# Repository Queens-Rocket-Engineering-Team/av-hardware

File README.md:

# Avionics Hardware
> 2026-2027 SRAD Avionics Hardware Repository

This repository contains **schematics**, **PCB layouts**, and related **documentation and datasheets** for QRET SRAD Avionics. 
- All ECAD was designed in or transferred to **KiCad 10**.
- Covers **all** avionics systems, including power, propulsion, recovery, telemetry, and shared libraries.
- The **main** branch contains the latest stable hardware that is not currently under active development.
- If you're contributing, please read over the [`Development Standards`](#development-standards) section.
---

## Folder Structure
Avionics systems are organized into root-level directories (e.g., `power/`, `telemetry/`, etc.). 

Each system contains folders per boards and a respective documentation file `README.MD`

Each board follows the structure below:
- `docs`: Board-specific documentation, datasheets, and other reference materials. 
- `symbols`: Board-specific schematic symbols.
- `footprints`: Board-specific PCB footprints.
- `models`: Board-specific component 3D-models.

**Example Structure**
```
av-hardware/
  power/
    README.md
    power-module/
      power-module.kicad_pro
      power-module.kicad_sch
      power-module.kicad_pcb
      docs/
        README.md
        datasheets/
      symbols/
      footprints/
      models/
```

## Development Standards
- **Always** ensure you've fetched and pulled from Git before contributing.
```
git fetch origin
git pull
```
- Keep `main` stable. Never make changes directly on `main`.
- If contributing, use focused, concise, and descriptive branch names and commit messages. Look at standards below.
- Commit changes on your branch frequently, don't leave changes hanging.

### Datasheet Naming Convention
- For ICs and other active components, download and attach the component's datasheet with the following name convention:
`[type]-[part-number].pdf`

For example:
- `ADC-ADS131M04.pdf`
  
### Branches
Contribute by creating a branch.

**Naming Conventions**
- Creating a new board: `dev/<description>`
- Updating or adding a feature to an existing board: `feature/board/<description>`
- Resolving an issue on an existing board: `fix/board/<description>`
- Updating documentation and reference materials: `docs/<description>`

For example:
- `dev/camera-module`
- `feature/power-module/change-buck`
- `fix/lcm/can-trx`

### Commits
Commit messages should be focused, concise, and descriptive. Each commit should represent a single logical change.
- You should try and commit after making a **single change**, rather than committing for several changes at once.

**Examples**
```text
Setup schematic env for camera module
Tune differential pair lengths
Update comms module with new LoRa module
Review updated comms module
```

### Pull Requests
Pull requests should clearly describe the changes being introduced and their purpose.

Before opening a pull request:

- Ensure the branch is up to date with `main`.
- Ensure all work and changes are peer-reviewed in person during meetings or office hours.
- Confirm that no unrelated changes are included.

**Title Convention**

```text
<type/board-name>: <short-description>
```
For example:
```text
feature/power-module: Change buck converter
fix/lcm: Switch to standard CAN transceiver
dev/camera-module: Initial design
docs/gps-antenna: Add images to documentation
```

## Comments
- You will likely encounter different schematic "formats" as you look through this repository. As of 2026, we are pushing the use of **hierarchical sheets** to improve modularity and readability. Previously, schematics were designed on a single, large sheet.

If you're ever unsure about anything, reach out to one us leads!!

---
QRET, 2026-2027

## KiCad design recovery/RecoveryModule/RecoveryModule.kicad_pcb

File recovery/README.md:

# [System Name]

this is a template and will be filled out soon

[Description of the  system and its purpose]

## Boards

- `[board-name]` - Brief description
- ...

---
QRET, 2026-2027

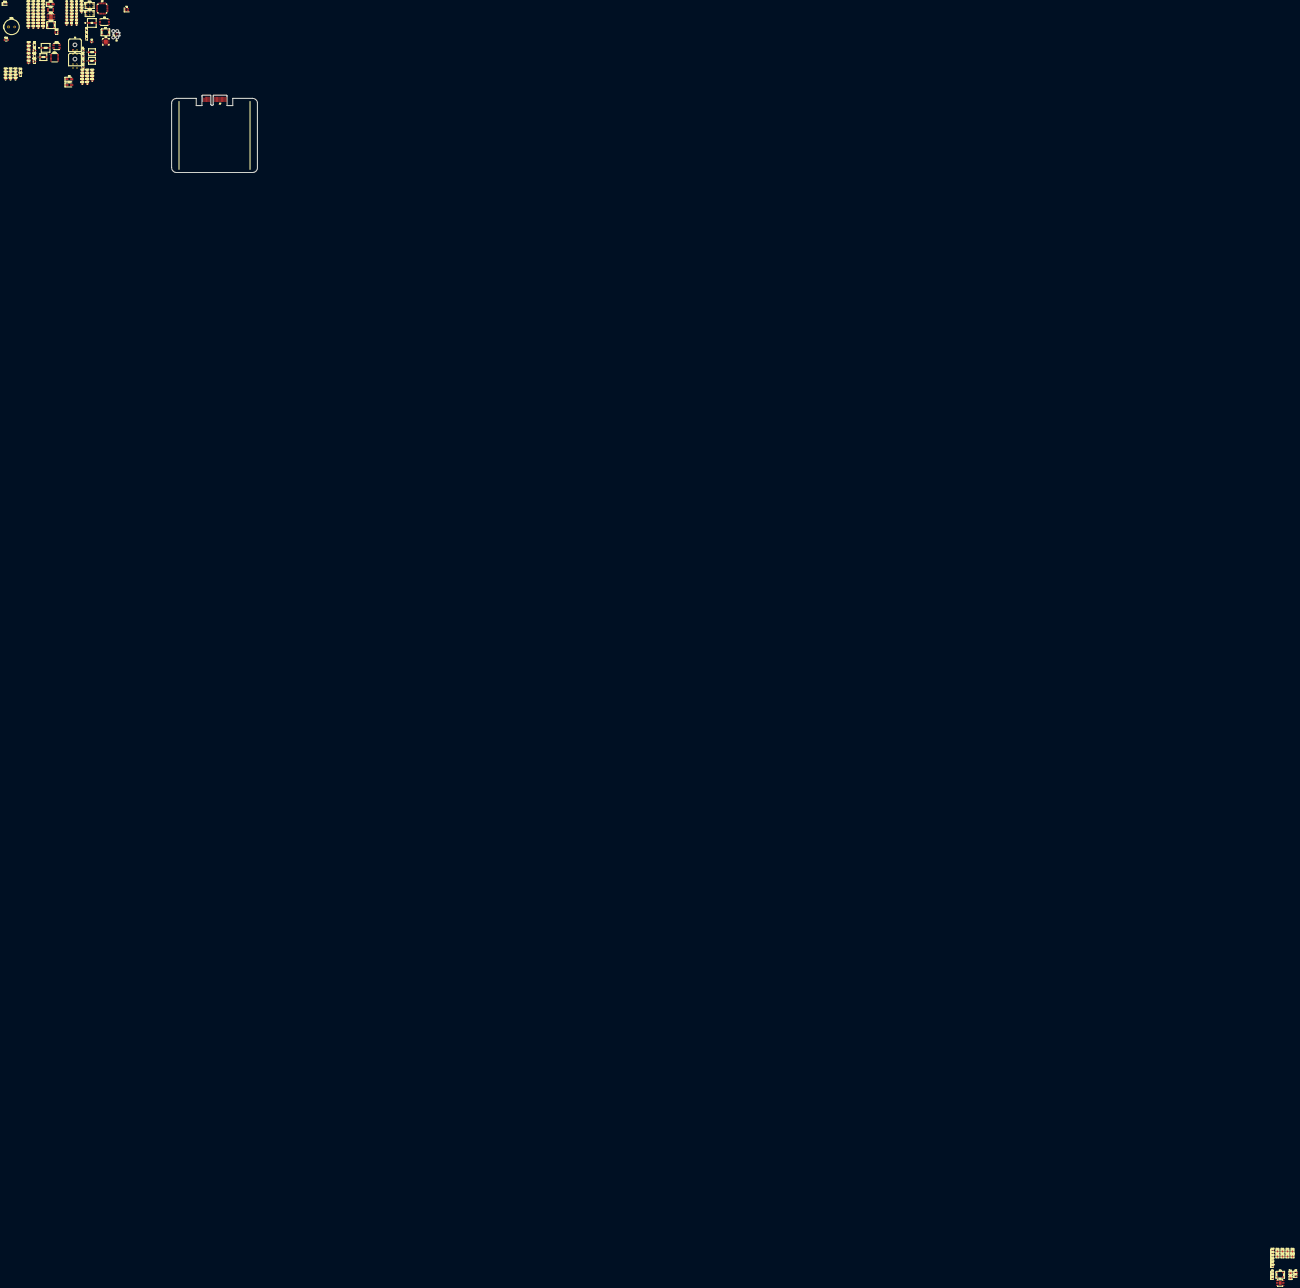
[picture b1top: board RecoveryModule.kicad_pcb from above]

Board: 2 copper layers, 161 parts (0 on the bottom side), 76 nets, no tracks yet.

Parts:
BZ1: Buzzer; Buzzer_TDK_PS1240P02BT_D12.2mm_H6.5mm
C1, C2, C3, C6, C7, C8, C9, C10, C11, C12, C15, C17, C19, C20, C21, C24, C26, C29, C31, C34, C36, C37, C40, C43, C46, C47, C48, C50, C51, C52, C54: 100n; C_0603_1608Metric
C4, C33: 100u; PCAP_6.3x7.7-ELECT_NCA
C5, C41, C42, C44, C45: 22u; C_0805_2012Metric
C13, C18, C22, C23, C49, C53: 4u7; C_0603_1608Metric
C14, C16: 18p; C_0603_1608Metric
C25, C27, C35: 47u; CAP_UCD_5X5P8_NCH
C28, C38: 10u; C_0805_2012Metric
C30: 220n; C_0603_1608Metric
C32: 1u; C_0603_1608Metric
C39: 47p; C_0603_1608Metric
D1: USB LED; LED_0603_1608Metric
D2: DBG_LED; LED_0603_1608Metric
D3: STAT_LED; LED_0603_1608Metric
D4: WS2812B; LED_Cree-PLCC4_5x5mm_CW
D5, D12: WS2812C; LED_Cree-PLCC4_5x5mm_CW
D6, D8, D10: SMAJ10A; D_SMA
D7: MAIN_ACTIVE; LED_0805_2012Metric
D9: DROGUE_ACTIVE; LED_0805_2012Metric
D11: BZT52C10; D_SOD-123
D13: 3V3_BP; LED_0603_1608Metric
D14: 3V3_REG; LED_0603_1608Metric
D15: 5V LED; LED_0603_1608Metric
D16: 5V_BP LED; LED_0603_1608Metric
D17: VBUS LED; LED_0603_1608Metric
D18: 5V_BATT LED; LED_0603_1608Metric
F1: MINISMDC200F/16-2; Fuse_1812_4532Metric
FB1: FerriteBead; R_1206_3216Metric
J1: Conn_01x04; Tag-Connect_TC2030-IDC-FP_2x03_P1.27mm_Vertical
J4: MAIN_EMATCH; Molex_Micro-Fit_3.0_43045-0400_2x02_P3.00mm_Horizontal
J5: DROGUE_EMATCH; Molex_Micro-Fit_3.0_43045-0400_2x02_P3.00mm_Horizontal
J7: Stack Male Edge Connector; BUS_PCIexpress_x1
Q1, Q2, Q3, Q4, Q5: AO3400A; SOT-23
Q6: BSS84; SOT-23
R1, R2, R10, R11, R12, R13, R21, R22, R24, R25, R27, R28, R30, R31, R35: 10k; R_0603_1608Metric
R3, R4: 5k1; R_0603_1608Metric
R5: 330R; R_0603_1608Metric
R6, R42, R43, R45: 150R; R_0603_1608Metric
R7: 50R; R_0603_1608Metric
R8: 22k; R_0603_1608Metric
R9: 47k; R_0603_1608Metric
R14, R15, R16, R17, R18, R19, R37, R40, R41: 2k2; R_0603_1608Metric
R20, R26: 200; R_0603_1608Metric
R23, R29: 1k; R_0603_1608Metric
R32: 100; SOT-23
R33: 10k; SOT-23
R34: 10k; TSSOP-20_4.4x6.5mm_P0.65mm
R36, R38, R46: 100k; R_0603_1608Metric
R39: 24.9k; R_0603_1608Metric
R44: 25m; R_0603_1608Metric
R47: 5k; R_0603_1608Metric
R48, R49, R50, R51: 300R; R_0603_1608Metric
SW1, SW2: SW_Push; SW_NKK_GW12LJP
TP1: CMAIN; TestPoint_Pad_2.0x2.0mm
TP2: CDROGUE; TestPoint_Pad_2.0x2.0mm
TP3: VIN_JUMP; TestPoint_Pad_2.0x2.0mm
TP4: +3.3V_BP; TestPoint_Pad_2.0x2.0mm
TP5: +3.3V_REG; TestPoint_Pad_2.0x2.0mm
TP6: +3.3V; TestPoint_Pad_2.0x2.0mm
TP7: +5V; TestPoint_Pad_2.0x2.0mm
TP8: +5V_BP; TestPoint_Pad_2.0x2.0mm
TP9: VBUS; TestPoint_Pad_2.0x2.0mm
TP10: +5V_BATT; TestPoint_Pad_2.0x2.0mm
U1: TCAN1051HGVDR; SOIC-8-1EP_3.9x4.9mm_P1.27mm_EP2.29x3mm
U2, U4, U5, U11, U12: TPD2E2U06DCK; SOT-323_SC-70
U3: W25Q128JVS; SOIC-8_5.3x5.3mm_P1.27mm
U7: STM32F103C8T6; LQFP-48_7x7mm_P0.5mm
U8: CP2102N; QFN-28-1EP_5x5mm_P0.5mm_EP3.35x3.35mm
U14: LMR33630ADDA; Texas_HSOP-8-1EP_3.9x4.9mm_P1.27mm_ThermalVias
U17: TLV75733PDBV; SOT-23-5
U18: DS2438Z_T_R; SOIC-8_3.9x4.9mm_P1.27mm
Y1: Crystal; Crystal_SMD_3225-4Pin_3.2x2.5mm

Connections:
+3.3V: C1.1, C2.2, C3.2, C4.2, C7.1, C8.1, C9.1, C10.1, C11.1, C13.1, C17.2, C18.1, C19.1, C20.1, C21.1, C22.1, C23.1, C32.1, C48.1, J1.2, R1.1, R2.1, R10.1, R11.1, R14.1, R15.1, R16.1, R17.1, R18.1, R19.1, R25.1, R31.1, R36.2, R45.1, R47.1, SW2.2, TP1.1 (1_1), TP2.1 (1_1), TP6.1 (1_1), U1.3 (VCC), U1.8 (S), U3.8 (VCC), U7.1 (VBAT), U7.9 (VDDA), U7.24 (VDD), U7.27 (PB14), U7.28 (PB15), U7.36 (VDD), U7.48 (VDD), U8.6 (VDD), U8.7 (VREGIN), U14.6 (VCC)
+3.3V_BP: C46.1, J7.A1 (3.3V_A), J7.A2 (3.3V_A), R32.1, R41.1, R42.1, TP4.1 (1_1)
+3.3V_REG: C47.1, C52.1, C53.1, R43.1, TP5.1 (1_1), U17.5 (OUT)
+5V: C5.1, C6.1, C12.1, C43.1, C49.1, C51.1, C54.1, D4.1 (VDD), D5.1 (VDD), R48.1, TP7.1 (1_1), U17.1 (IN), U17.3 (EN), U18.5 (VDD)
+5V_BATT: C29.1, C39.1, C41.1, C42.1, C44.1, C45.1, R37.1, R38.1, R51.1, TP10.1 (1_1)
+5V_BP: C31.1, J7.A4 (5.0V_A), J7.A5 (5.0V_A), R49.1, TP8.1 (1_1)
/Power Interface/BCK_PG: R36.1, U7.41 (PB5), U14.4 (PG)
/Power Interface/BattMonitor_1WIRE: R47.2, U18.8 (DQ)
/Power Interface/CAN_N: J7.B13 (CAN_L), U1.7 (CANH), U5.1
/Power Interface/CAN_P: J7.B14 (CAN_H), U1.6 (CANL), U5.2
/PyroControl/DROGUE_EN: R26.2, U7.26 (PB13)
/PyroControl/MAIN_EN: R20.2, U7.25 (PB12)
/STM32F1 Breakout Circuitry/ARGB_DIN: D4.4 (DIN), U7.46 (PB9)
/STM32F1 Breakout Circuitry/BOOT0: R12.1, SW2.1, U7.44 (BOOT0)
/STM32F1 Breakout Circuitry/BOOT1: R13.2, U7.20 (PB2)
/STM32F1 Breakout Circuitry/CAN_RX: U1.4 (RXD), U7.32 (PA11)
/STM32F1 Breakout Circuitry/CAN_TX: U1.1 (TXD), U7.33 (PA12)
/STM32F1 Breakout Circuitry/CS_FL: U3.1 (~CS), U7.14 (PA4)
/STM32F1 Breakout Circuitry/DBG_LED: R6.2, U7.18 (PB0)
/STM32F1 Breakout Circuitry/GPS_EXTINT: U7.11 (PA1), U12.2
/STM32F1 Breakout Circuitry/GPS_~RST: U7.10 (PA0), U12.1
/STM32F1 Breakout Circuitry/MCU_RESET: C15.1, R10.2, SW1.1
/STM32F1 Breakout Circuitry/MISO_FL: U3.5 (DI/IO_{0}), U7.16 (PA6)
/STM32F1 Breakout Circuitry/MOSI_FL: U3.2 (DO/IO_{1}), U7.17 (PA7)
/STM32F1 Breakout Circuitry/RESET_FL: R1.2, U3.7 (~HOLD/~RESET/IO_{3}), U7.29 (PA8)
/STM32F1 Breakout Circuitry/SCK_FL: U3.6 (CLK), U7.15 (PA5)
/STM32F1 Breakout Circuitry/STAT_LED: R7.2, U7.19 (PB1)
/STM32F1 Breakout Circuitry/SWCLK: J1.4, U2.1
/STM32F1 Breakout Circuitry/SWDIO: J1.3, U2.2, U7.34 (PA13)
/STM32F1 Breakout Circuitry/USB_D+: U4.2, U8.4 (D+)
/STM32F1 Breakout Circuitry/USB_D-: U4.1, U8.5 (D-)
/STM32F1 Breakout Circuitry/USB_RX: U7.30 (PA9), U8.25 (RXD)
/STM32F1 Breakout Circuitry/USB_TX: U7.31 (PA10), U8.26 (TXD)
/STM32F1 Breakout Circuitry/WP_FL: R2.2, U3.3 (~WP/IO_{2}), U7.45 (PB8)
/STM32F1 Breakout Circuitry/XTAL_IN: C14.1, U7.3 (PC14), Y1.1
/STM32F1 Breakout Circuitry/XTAL_OUT: C16.1, U7.4 (PC15), Y1.2
/Sensor Interface/I2C1_SCL: R14.2, R15.2
/Sensor Interface/I2C1_SDA: R16.2, R17.2
/Sensor Interface/I2C2_SCL: R19.2, U11.1
/Sensor Interface/I2C2_SDA: R18.2, U11.2
GND: C1.2, C2.1, C3.1, C4.1, C5.2, C6.2, C7.2, C8.2, C9.2, C10.2, C11.2, C12.2, C13.2, C14.2, C15.2, C16.2, C17.1, C18.2, C19.2, C20.2, C21.2, C22.2, C23.2, C28.2, C29.2, C30.2, C31.2, C32.2, C34.2, C36.2, C41.2, C42.2, C43.2, C44.2, C45.2, C46.2, C47.2, C48.2, C49.2, C50.2, C51.2, C52.2, C53.2, C54.2, D1.1 (K), D2.1 (K), D3.1 (K), D4.3 (VSS), D5.3 (VSS), D6.2 (A2), D7.1 (K), D8.2 (A2), D9.1 (K), D10.2 (A2), D12.1 (K), D13.1 (K), D14.1 (K), D15.1 (K), D16.1 (K), D17.1 (K), D18.1 (K), J1.1, J7.A3 (GND_A), J7.A6 (GND_A), J7.B4 (GND_A), J7.B5 (GND_A), J7.B6 (GND_A), Q1.3 (S), Q2.3 (S), Q3.3 (S), Q4.3 (S), Q5.2 (S), R3.1, R4.1, R9.2, R12.2, R13.1, R21.2, R24.2, R27.2, R30.2, R33.2, R34.1, R39.2, R44.1, R44.2, R46.1, SW1.2, U1.2 (GND), U2.3, U3.4 (GND), U4.3, U5.3, U7.8 (VSSA), U7.23 (VSS), U7.35 (VSS), U7.47 (VSS), U8.3 (GND), U8.29 (GND), U11.3, U12.3, U14.1 (GND), U14.9 (GND), U17.2 (GND), U18.1 (GND), U18.2 (VSENS+)
unnamed: D1.2 (A), R5.2
unnamed: D2.2 (A), R6.1
unnamed: D3.2 (A), R7.1
unnamed: D4.2 (DOUT), D5.4 (DIN)
unnamed: C24.1, C25.2, D6.1 (A1), J4.1, Q1.1 (D), R22.1
unnamed: D7.2 (A), R23.1
unnamed: C26.1, C27.2, D8.1 (A1), J5.1, Q3.1 (D), R28.2
unnamed: D9.2 (A), R29.2
unnamed: D10.1 (A1), F1.2, Q6.3 (D)
unnamed: C33.1, D11.2 (A), FB1.1, Q6.2 (S)
unnamed: C33.2, C35.2, C38.2, C40.2, D11.1 (K), Q6.1 (G), R34.2
unnamed: D12.2 (A), R42.2
unnamed: D13.2 (A), R43.2
unnamed: D14.2 (A), R45.2
unnamed: D15.2 (A), R48.2
unnamed: D16.2 (A), R49.2
unnamed: D17.2 (A), R50.2
unnamed: D18.2 (A), R51.2
unnamed: Q1.2 (G), R20.1, R21.1
unnamed: Q2.1 (D), R25.2
unnamed: Q2.2 (G), R22.2, R24.1
unnamed: Q3.2 (G), R26.1, R27.1
unnamed: Q4.1 (D), R31.2
unnamed: Q4.2 (G), R28.1, R30.1
unnamed: Q5.3 (D), R35.2, U14.3 (EN)
unnamed: Q5.1 (G), R32.2, R33.1
unnamed: R8.2, R9.1, U8.8 (VBUS)
unnamed: R11.2, U8.9 (~RST)
unnamed: C37.1, U14.7 (BOOT)
unnamed: C39.2, R38.2, R39.1, U14.5 (FB)
unnamed: C37.2, U14.8 (SW)
unnamed: C34.1, R40.1
unnamed: C50.1, R46.2, U18.3 (VSENS-)
VBATT: C24.2, C25.1, C26.2, C27.1, C28.1, C30.1, C35.1, C38.1, C40.1, FB1.2, J4.2, J5.2, R23.2, R29.1, R35.1, TP3.1 (1_1), U14.2 (VIN)
VBUS: C36.1, R5.1, R8.1, R50.1, TP9.1 (1_1)

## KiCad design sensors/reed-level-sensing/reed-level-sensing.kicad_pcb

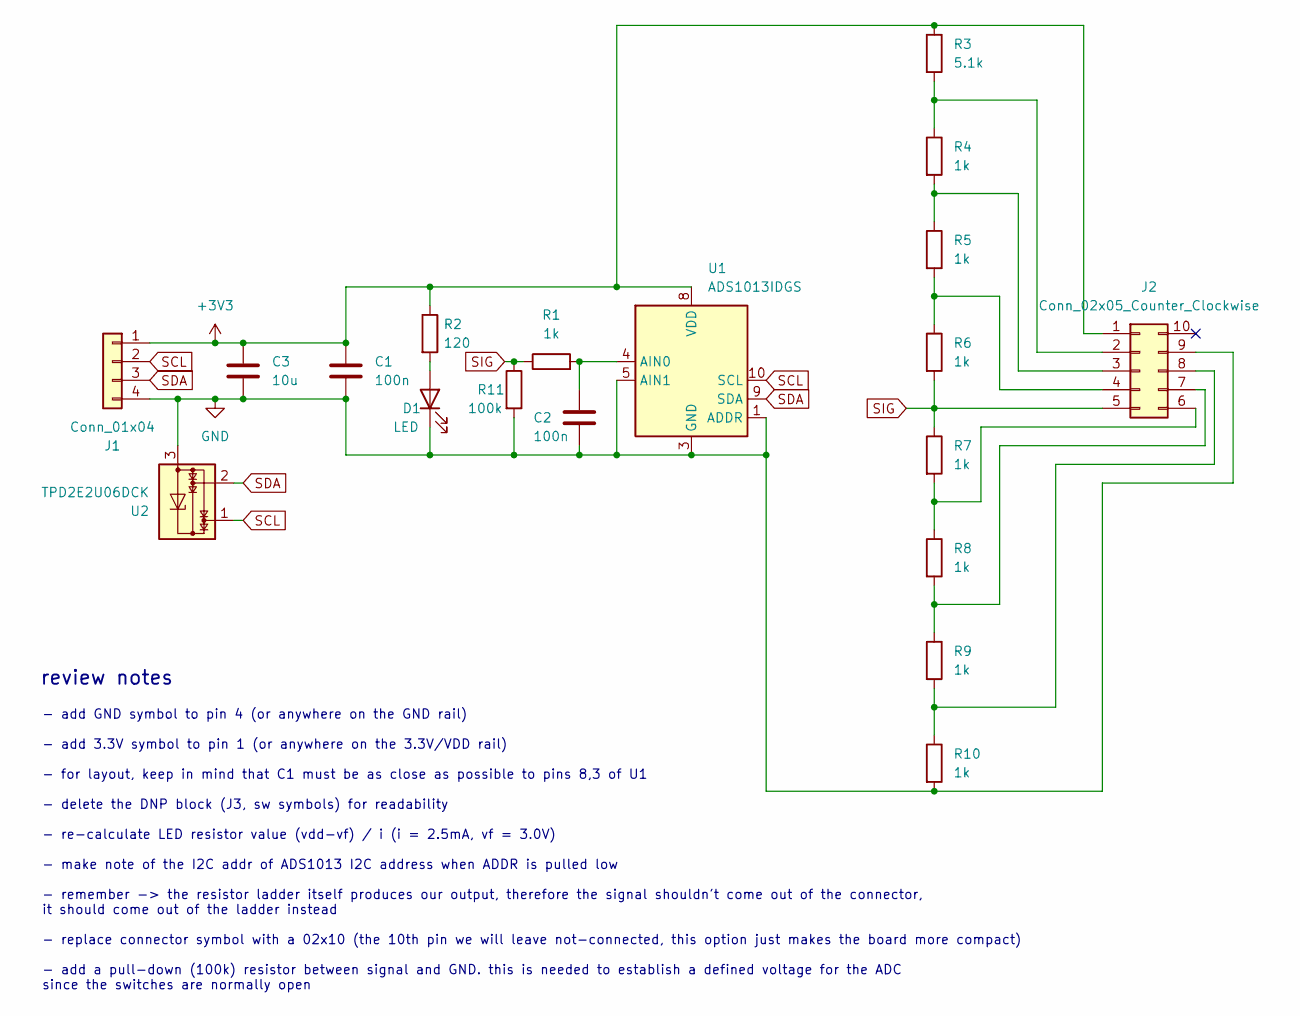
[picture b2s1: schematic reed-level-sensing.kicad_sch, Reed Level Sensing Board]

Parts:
C1, C2: 100n; C_0603_1608Metric_Pad1.08x0.95mm_HandSolder
C3: 10u; C_0805_2012Metric_Pad1.18x1.45mm_HandSolder
D1: LED; SOT-323_SC-70
J1: Conn_01x04; Molex_Nano-Fit_105313-xx04_1x04_P2.50mm_Horizontal
J2: Conn_02x05_Counter_Clockwise
R1, R4, R5, R6, R7, R8, R9, R10: 1k; R_0603_1608Metric_Pad0.98x0.95mm_HandSolder
R2: 120; R_0603_1608Metric_Pad0.98x0.95mm_HandSolder
R3: 5.1k; R_0603_1608Metric_Pad0.98x0.95mm_HandSolder
R11: 100k
U1: ADS1013IDGS; TSSOP-10_3x3mm_P0.5mm
U2: TPD2E2U06DCK; SOT-323_SC-70

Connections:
+3V3: C1.1, C3.1, J1.1, J2.1, R2.1, R3.1, U1.8 (VDD)
GND: C1.2, C2.2, C3.2, D1.1 (K), J1.4, J2.9, R10.2, R11.2, U1.1 (ADDR), U1.3 (GND), U1.5 (AIN1), U2.3
unnamed: D1.2 (A), R2.2
unnamed: J2.2, R3.2, R4.1
unnamed: J2.3, R4.2, R5.1
unnamed: J2.4, R5.2, R6.1
unnamed: J2.6, R7.2, R8.1
unnamed: J2.7, R8.2, R9.1
unnamed: J2.8, R9.2, R10.1
unnamed: C2.1, R1.2, U1.4 (AIN0)
SCL: J1.2, U1.10 (SCL), U2.1
SDA: J1.3, U1.9 (SDA), U2.2
SIG: J2.5, R1.1, R6.2, R7.1, R11.1

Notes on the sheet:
- add GND symbol to pin 4 (or anywhere on the GND rail) - add 3.3V symbol to pin 1 (or anywhere on the 3.3V/VDD rail) - for layout, keep in mind that C1 must be as close as possible to pins 8,3 of U1 - delete the DNP block (J3, sw symbols) for readability - re-calculate LED resistor value (vdd-vf) 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
review notes

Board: 2 copper layers, 19 parts (0 on the bottom side), 13 nets, no tracks yet.

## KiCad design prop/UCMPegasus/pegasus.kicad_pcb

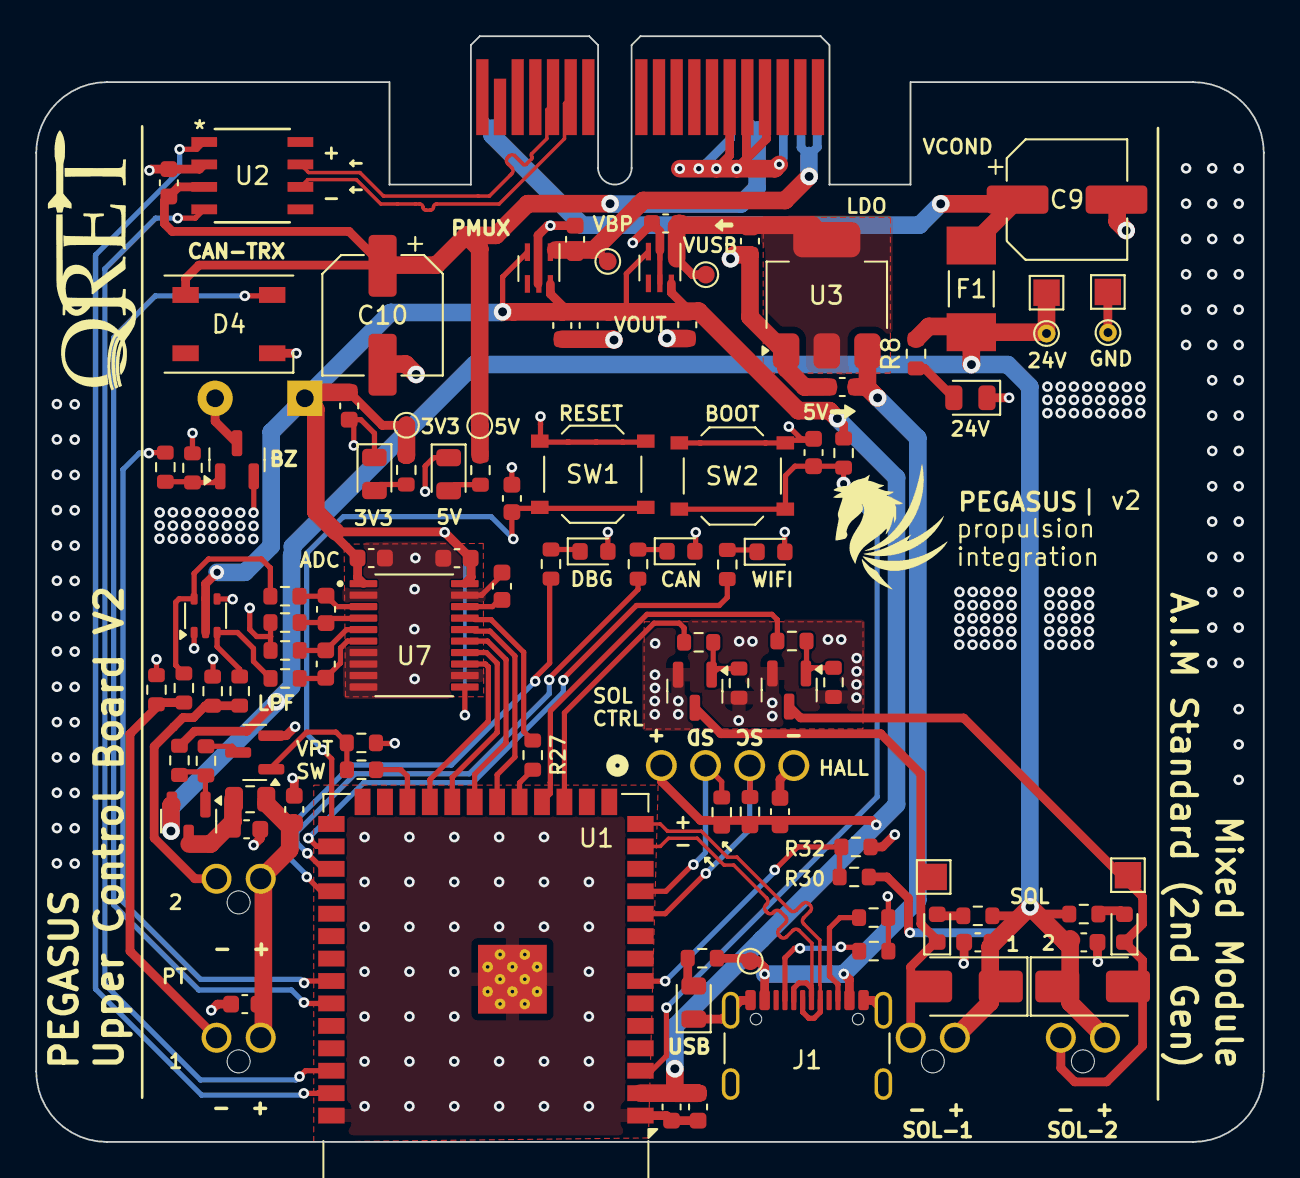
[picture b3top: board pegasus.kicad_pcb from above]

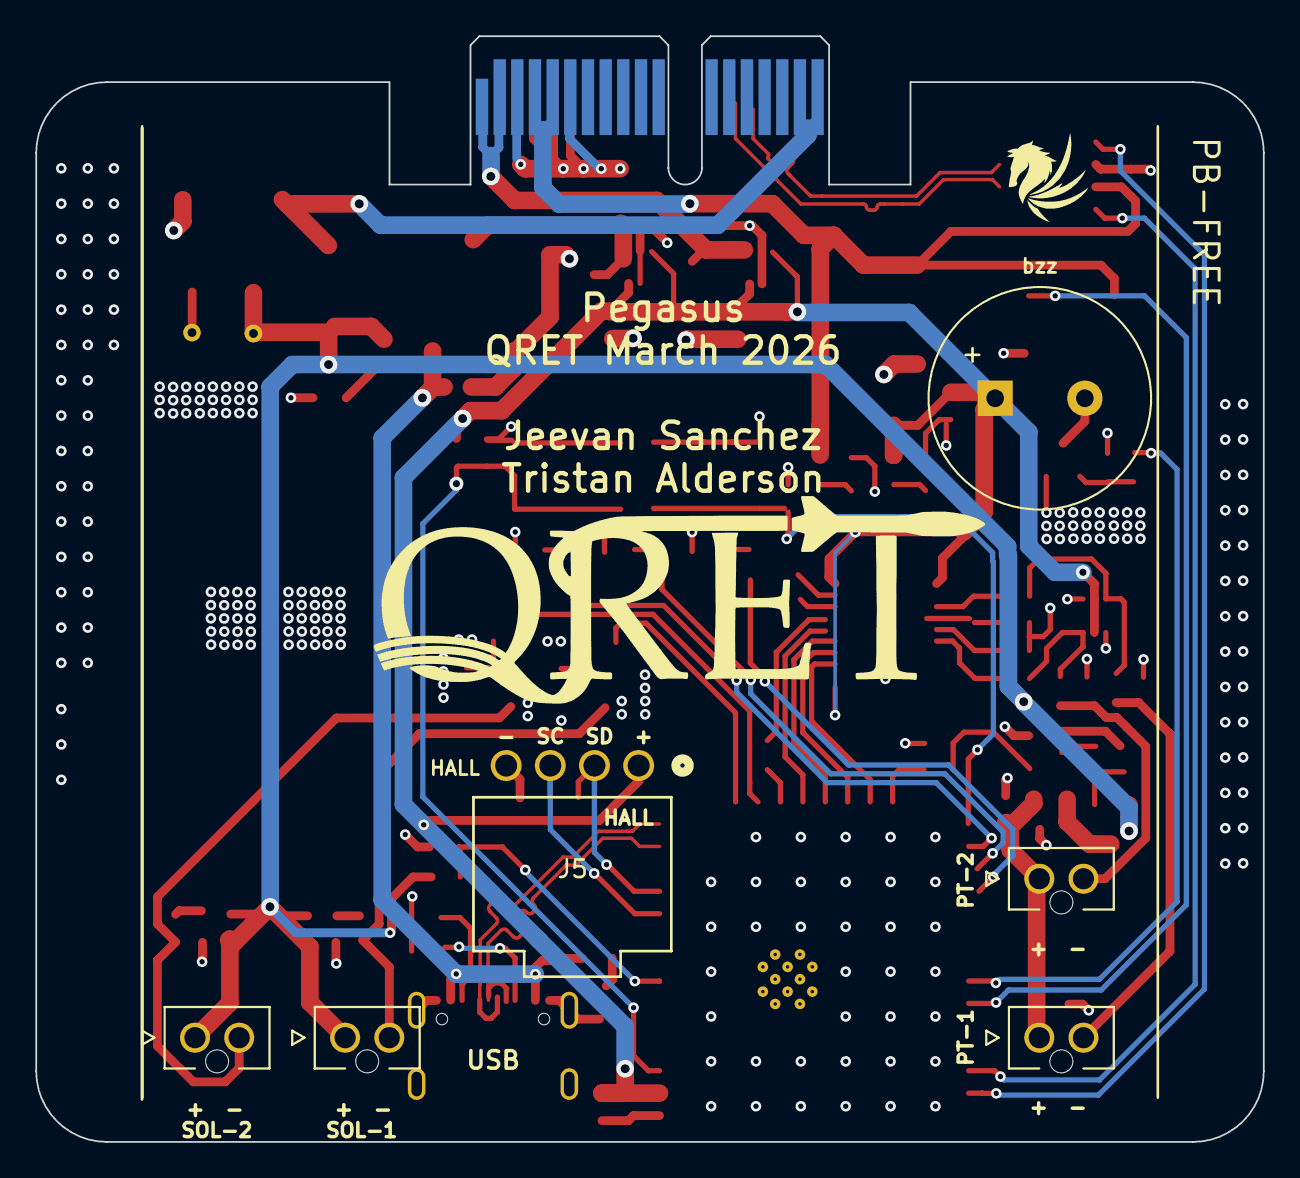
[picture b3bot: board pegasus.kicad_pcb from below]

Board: 4 copper layers, 69.5 x 62.6 mm, 108 parts (6 on the bottom side), 64 nets.

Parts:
BZ1: PS1240P02BT; Buzzer_12.6x9.5RM5.0
C1, C11, C12, C29, C31: 1uF; C_0603_1608Metric
C2, C4, C6, C7, C16, C18, C22, C23: 100nF; C_0603_1608Metric
C3, C5, C8, C14, C17: 10uF; C_0603_1608Metric
C9: 100uF; CP_Elec_6.3x5.9
C10: 100uF 16V; CP_Elec_6.3x5.9
C13, C24: 0.1uF; C_0603_1608Metric
C15: 1nF; C_0603_1608Metric
C25, C26: 10nF; C_0603_1608Metric
C30: 220 nF; C_0603_1608Metric
D1: FAULT_LED (RED); LED_0603_1608Metric
D2: CAN_LED (WHT); LED_0603_1608Metric
D3: WIFI_LED (WHT); LED_0603_1608Metric
D4: SYS_LED_WS2812B; LED_WS2812B_PLCC4_5.0x5.0mm_P3.2mm
D5: PWR_3V3_LED (GRN); LED_0805_2012Metric
D6: PWR_24V_LED (GRN); LED_0805_2012Metric
D7: PWR_5V_LED (GRN); LED_0805_2012Metric
D8: USB_LED (GRN); LED_0805_2012Metric
D9: SOL2_LED (WHT); LED_0603_1608Metric
D10: SOL1_LED (WHT); LED_0603_1608Metric
D11, D12: SS34; D_SMA
D13: BAV199DW; SOT-363_SC-70-6
F1: Fuse; FUSC6125X279N
FB1: 100R; R_0805_2012Metric
J1: USB_C_Female_USB2_Small; USB_C_Receptacle_GCT_USB4105-xx-A_16P_TopMnt_Horizontal
J2: Stack Male Edge Connector; BUS_PCIexpress_x1
J3, J4: SOL_CONN; MOLEX_1053091102
J5: HALL-1; CONN_SD-105313-100_04_MOL
J6, J7: PT; MOLEX_1053091102
Q1, Q2: AO3400A; SOT-23
Q4, Q5: 2N7002; SOT-23
R1, R23, R28, R32, R38: 10k; R_0603_1608Metric
R2: 680; R_0603_1608Metric
R3, R4: 270; R_0603_1608Metric
R5, R6: 5.1k; R_0603_1608Metric
R7: 3.3k; R_0603_1608Metric
R8, R15, R16: 12k; R_0603_1608Metric
R9, R29, R37: 6.2k; R_0603_1608Metric
R10, R11, R13, R19, R31, R39: 200; R_0603_1608Metric
R12, R14, R30: 100k; R_0603_1608Metric
R17, R20: 62; R_0603_1608Metric
R18, R26: 1k; R_0603_1608Metric
R21, R22: 2.2k; R_0603_1608Metric
R24, R25: 1.2k; R_0603_1608Metric
R27: 33; R_0603_1608Metric
SW1: SW_ESP_BOOT_MODE; SW_Push_1P1T_XKB_TS-1187A
SW2: SW_ESP_RESET; SW_Push_1P1T_XKB_TS-1187A
TP1: 5V_USB; TestPoint_Pad_D1.0mm
TP2: 3V3-TP; TestPoint_Pad_D1.0mm
TP3: 24V-TP-P; TestPoint_Pad_1.5x1.5mm
TP4: 5V-TP; TestPoint_Pad_D1.0mm
TP5: GND-TP-P; TestPoint_Pad_1.5x1.5mm
TP6: 3V3_BP; TestPoint_Pad_D1.0mm
TP7: GND-TP-H; TestPoint_THTPad_D1.0mm_Drill0.5mm
TP8: VALVE2_OUT_TP; TestPoint_Pad_1.5x1.5mm
TP9: 3V3_USB; TestPoint_Pad_D1.0mm
TP10: VALVE1_OUT_TP; TestPoint_Pad_1.5x1.5mm
TP11: 24V-TP-H; TestPoint_THTPad_D1.0mm_Drill0.5mm
U1: ESP32-S3-WROOM-1-N16; ESP32-S3-WROOM-1
U2: TCAN1051HGVDR; SOIC_1044BDR_TEX
U3: AMS1117-3.3; SOT-223-3_TabPin2
U4, U5: ID_LM66100DCKR; SC-70-6
U7: ADC_ADS131M04IPWR; SOP65P640X120-20N
U9: DMP4065S-7; SOT-23

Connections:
5V_USB: C14.1, J1.A4 (VBUS), J1.A9 (VBUS), J1.B4 (VBUS), J1.B9 (VBUS), R29.1, TP1.1, U3.3 (VI)
24V_SENSE: R30.2, R32.2, U1.7 (IO7)
+3V3: BZ1.1 (+), C2.1, C3.1, C15.1, C16.1, C17.1, C22.2, C23.1, C29.2, C31.2, D13.2 (K2), D13.5 (K4), J5.1, R1.1, R7.2, R21.2, R22.1, TP2.1, U1.2 (3V3), U4.3 (*CE), U4.6 (VOUT), U5.3 (*CE), U5.6 (VOUT), U7.1 (AVDD), U7.11 (~SYNC/~RESET), U7.20 (DVDD)
+5V: C6.2, C10.1, D4.1 (VDD), J2.A4 (5.0V_A), J2.A5 (5.0V_A), R9.2, TP4.1, U2.3 (VCC)
+24V: C7.1, C18.1, D11.1 (K), D12.1 (K), F1.1, J3.1, J4.1, R8.2, R15.2, R16.2, R30.1, R37.2, TP3.1, TP11.1, U9.2 (S)
+24V_BP: C9.1, F1.2, J2.A17 (24V_A), J2.A18 (24V_A)
/ESP32-S3 Breakout Circuitry/BUZZ_EN: R10.2, U1.34 (IO41)
/ESP32-S3 Breakout Circuitry/CAN_LED: R3.1, U1.29 (IO36)
/ESP32-S3 Breakout Circuitry/CAN_RX: U1.38 (IO2), U2.4 (RXD)
/ESP32-S3 Breakout Circuitry/CAN_TX: U1.39 (IO1), U2.1 (TXD)
/ESP32-S3 Breakout Circuitry/DEBUG_LED: R2.1, U1.30 (IO37)
/ESP32-S3 Breakout Circuitry/ESP32_EN: C1.1, R1.2, SW2.2, U1.3 (EN)
/ESP32-S3 Breakout Circuitry/ESP32_IO0: C4.2, SW1.2, U1.27 (IO0)
/ESP32-S3 Breakout Circuitry/RGB_DATAIN: D4.4 (DIN), U1.35 (IO42)
/ESP32-S3 Breakout Circuitry/USB_N: J1.A7 (D-), J1.B7 (D-), U1.13 (USB_D-)
/ESP32-S3 Breakout Circuitry/USB_P: J1.A6 (D+), J1.B6 (D+), U1.14 (USB_D+)
/ESP32-S3 Breakout Circuitry/WIFI_LED: R4.1, U1.28 (IO35)
/Power Circuitry/3V3_BP: C11.2, J2.A1 (3.3V_A), J2.A2 (3.3V_A), TP6.1, U4.1 (VIN)
/Power Circuitry/3V3_USB: C5.1, C12.1, TP9.1, U3.2 (VO), U5.1 (VIN)
/Sensing Circuitry/PT1_CLAMPED: C25.2, R19.1, U7.3 (AIN0P)
/Sensing Circuitry/PT2_CLAMPED: C26.2, R31.1, U7.6 (AIN1P)
ADC_CLK: R27.1, U7.17 (CLKIN)
ADC_DRDY: U1.23 (IO21), U7.13 (~DRDY)
ADC_MISO: U1.21 (IO13), U7.15 (DOUT)
ADC_MOSI: U1.20 (IO12), U7.16 (DIN)
ADC_SCLK: U1.22 (IO14), U7.14 (SCLK)
CAN_N: J2.B13 (CAN_L), U2.6 (CANL)
CAN_P: J2.B14 (CAN_H), U2.7 (CANH)
GND: C1.2, C2.2, C3.2, C4.1, C5.2, C6.1, C7.2, C8.2, C9.2, C10.2, C11.1, C12.2, C13.2, C14.2, C15.2, C16.2, C17.2, C18.2, C22.1, C23.2, C24.2, C29.1, C30.2, C31.1, D1.2 (A), D2.2 (A), D3.2 (A), D4.3 (VSS), D5.1 (K), D6.1 (K), D7.1 (K), D8.1 (K), D13.1 (A1), D13.4 (A3), J1.A1 (GND), J1.A12 (GND), J1.B1 (GND), J1.B12 (GND), J1.S1 (SHIELD), J2.A3 (GND_A), J2.A6 (GND_A), J2.B4 (GND_A), J2.B5 (GND_A), J2.B6 (GND_A), J5.4, Q1.2 (S), Q2.2 (S), Q4.2 (S), Q5.2 (S), R5.2, R6.2, R12.1, R14.1, R17.1, R20.1, R24.1, R25.1, R28.1, R32.1, R38.1, SW1.1, SW2.1, TP5.1, TP7.1, U1.1 (GND), U1.40 (GND), U1.41 (GND), U2.2 (GND), U3.1 (ADJ), U4.2 (GND), U4.5 (ST), U5.2 (GND), U5.5 (ST), U7.2 (AGND), U7.7 (AIN2P), U7.8 (AIN2N), U7.9 (AIN3N), U7.10 (AIN3P), U7.12 (~CS), U7.19 (DGND)
HALL_SCL: J5.3, R22.2, U1.10 (IO17)
HALL_SDA: J5.2, R21.1, U1.11 (IO18)
unnamed: BZ1.2 (-), Q4.3 (D)
unnamed: D1.1 (K), R2.2
unnamed: D2.1 (K), R3.2
unnamed: D3.1 (K), R4.2
unnamed: D5.2 (A), R7.1
unnamed: D6.2 (A), R8.1
unnamed: D7.2 (A), R9.1
unnamed: D8.2 (A), R29.2
unnamed: D9.2 (A), R15.1
unnamed: D10.2 (A), R16.1
unnamed: D13.6 (K3A4), R18.2, R19.2
unnamed: D13.3 (K1A2), R26.2, R31.2
unnamed: J1.A5 (CC1), R5.1
unnamed: J1.B5 (CC2), R6.1
unnamed: J6.2, R17.2, R18.1
unnamed: J7.2, R20.2, R26.1
unnamed: Q1.1 (G), R11.1, R12.2
unnamed: Q2.1 (G), R13.1, R14.2
unnamed: Q4.1 (G), R10.1, R28.2
unnamed: Q5.3 (D), R23.1
unnamed: Q5.1 (G), R38.2, R39.2
unnamed: R27.2, U1.19 (IO11)
unnamed: C25.1, R24.2, U7.4 (AIN0N)
unnamed: C26.1, R25.2, U7.5 (AIN1N)
unnamed: C30.1, U7.18 (CAP)
unnamed: C8.1, FB1.1, U9.3 (D)
unnamed: R23.2, R37.1, U9.1 (G)
SOL1_EN: R11.2, U1.17 (IO9)
SOL1_RET: D10.1 (K), D11.2 (A), J3.2, Q1.3 (D), TP10.1
SOL2_EN: R13.2, U1.18 (IO10)
SOL2_RET: D9.1 (K), D12.2 (A), J4.2, Q2.3 (D), TP8.1
VPT: C13.1, C24.1, FB1.2, J6.1, J7.1
VPT_EN: R39.1, U1.24 (IO47)

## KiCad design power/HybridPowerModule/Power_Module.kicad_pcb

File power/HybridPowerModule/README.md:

# [Board Name]

## Overview

Brief description of the board, its purpose, and its role within the [System Name] system.

## Electrical Characteristics

| Parameter | Value |
|-----------|-------|

## Specifications

### MCU

- **Part:** 
- **Architecture:** 
- **Clock:** 
- **Memory:** 

### Communications

### Other/Peripherals

- **Sensors:** 
- **Storage:** 
- **Connectors:** 

## System Partitioning
Brief, abstract overviews of the different subsystems across the board. Think of the board as the main system.
- A subsytem could be the board's power, the controlling cirucit of a main peripheral, etc.

### [Partition Name]

Description of the subsytem and its function.

### [Partition Name]

Description of the substeym and its function.

...
## Hardware

### Major Hardware Components

- **[Component]**: Description
...

### Major Circuits

**[Circuit]**
- Description, supporting calculations, snippet of circuit.

## History
- Any relevant information on the board's histroy: issues, etc. 

## Status

**Status:** [Development / Review / Shipped / Assembly / Testing / Validated / ]

**Revision:** [Revision]

## Changelog

### [Revision]
- Description of change | Date
- Description of change | Date
...

---
QRET, 2026-2027

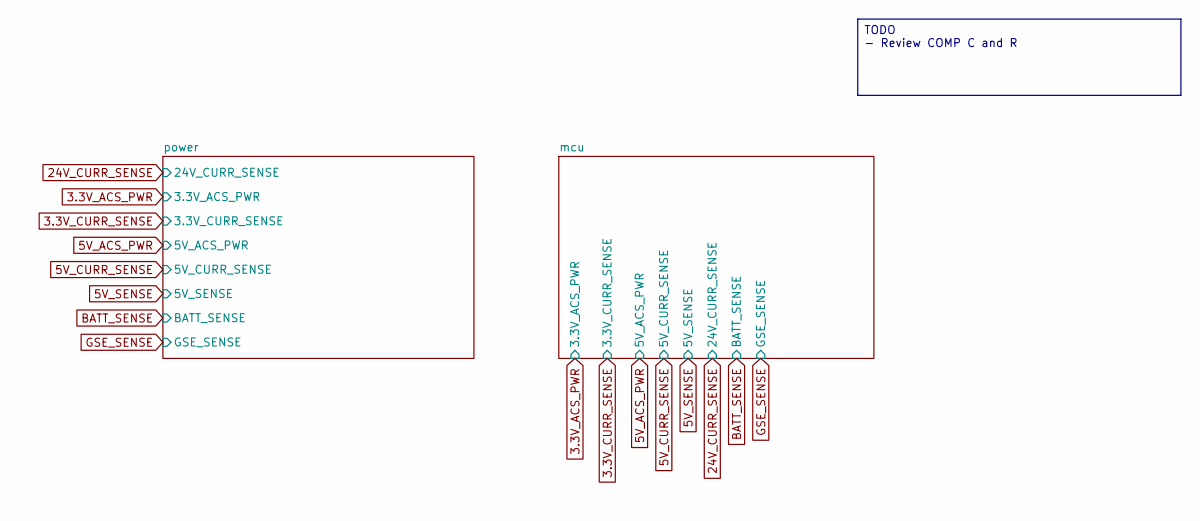
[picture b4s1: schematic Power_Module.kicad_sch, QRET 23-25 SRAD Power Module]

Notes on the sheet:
TODO - Review COMP C and R

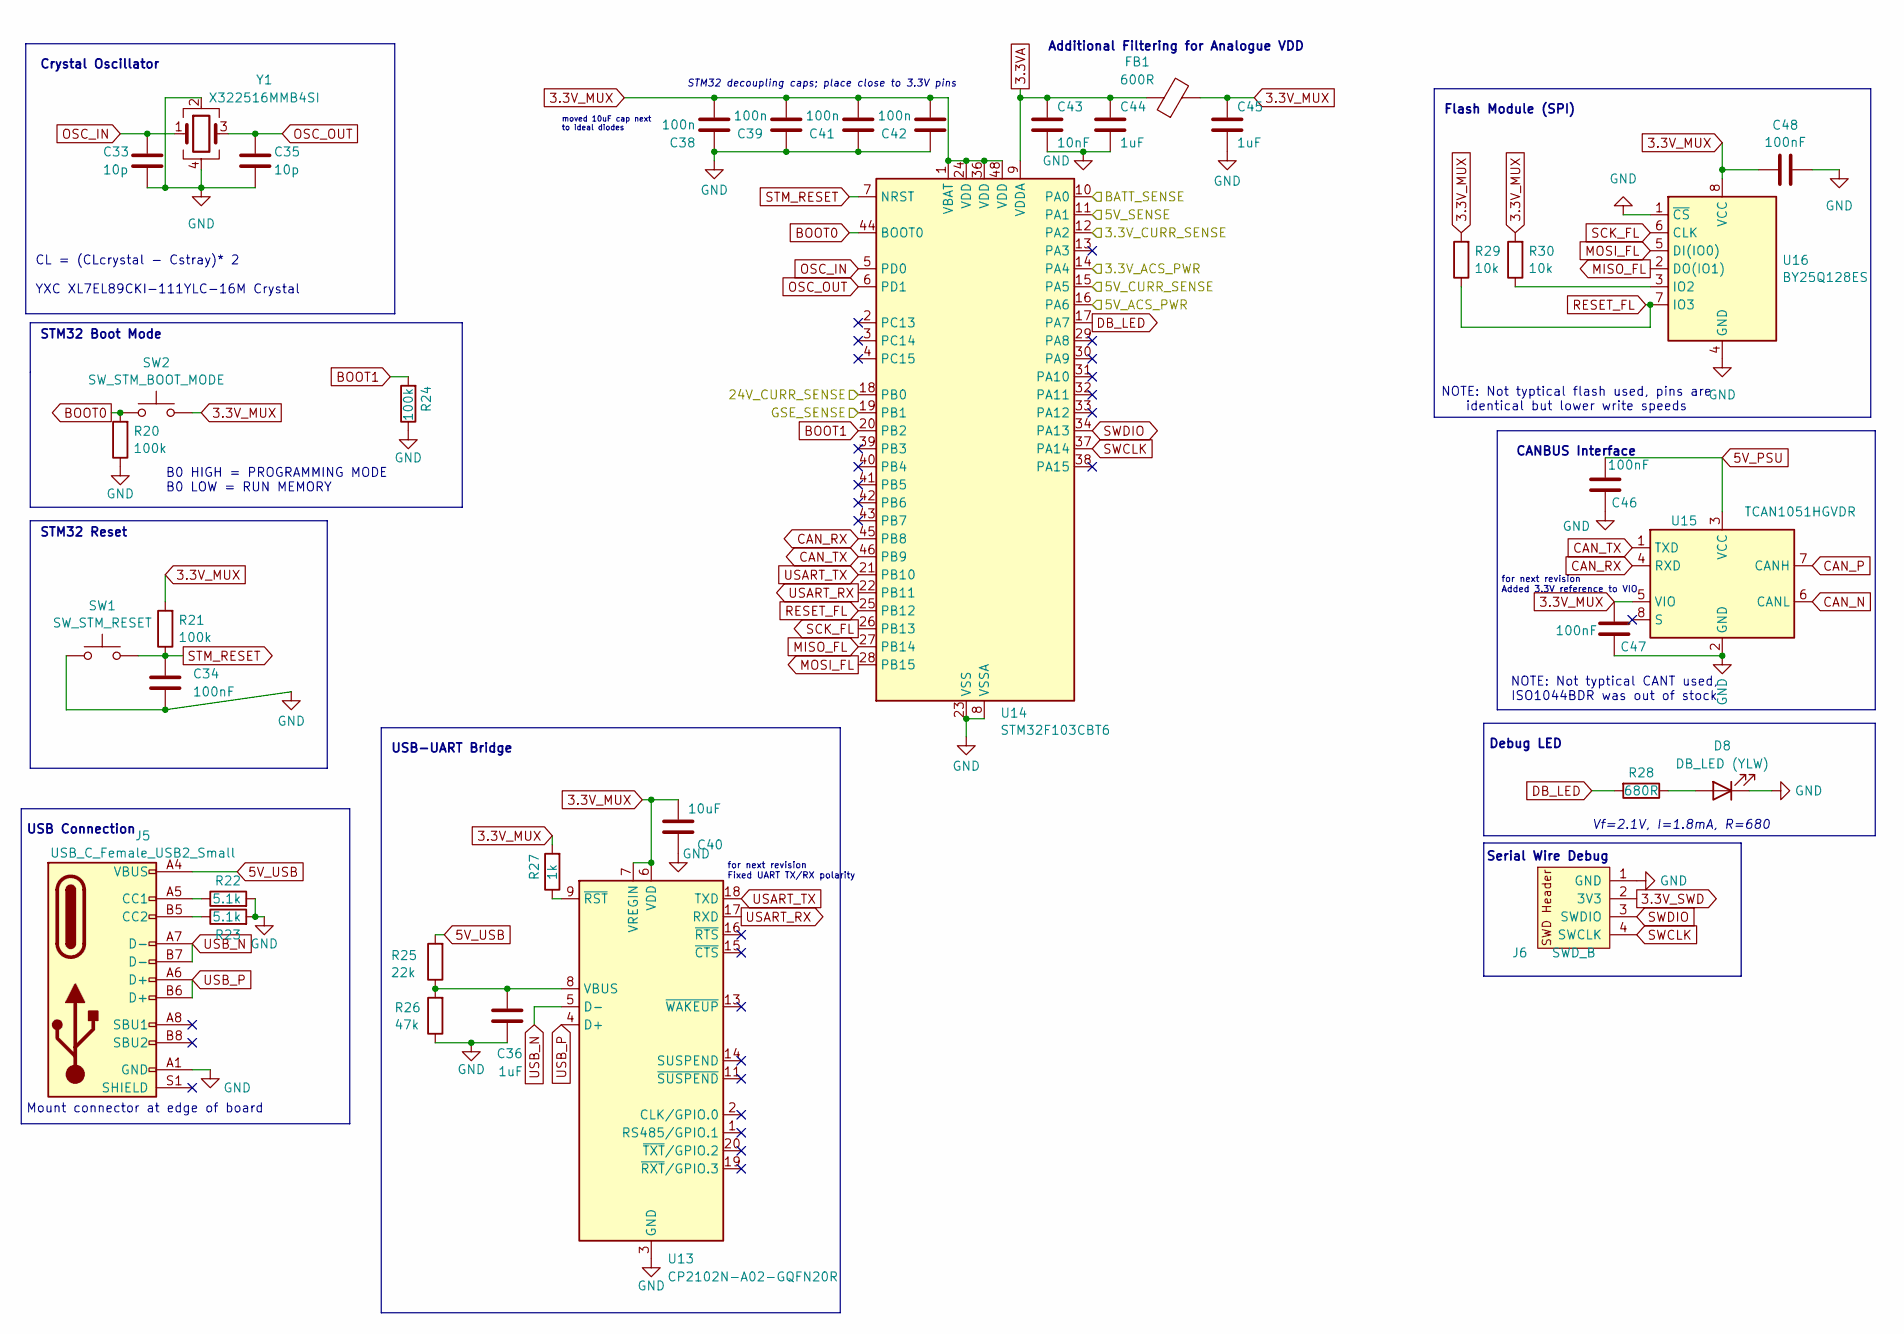
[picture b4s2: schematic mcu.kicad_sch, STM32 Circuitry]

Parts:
C33, C35: 10p; C_0402_1005Metric; LCSC C32949
C34, C46, C47, C48: 100nF; C_0603_1608Metric; LCSC C14663
C36, C44, C45: 1uF; C_0603_1608Metric; LCSC C15849
C38, C39, C41, C42: 100n; C_0402_1005Metric; LCSC C1525
C40: 10uF; C_0603_1608Metric; LCSC C96446
C43: 10nF; C_0603_1608Metric; LCSC C57112
D8: DB_LED (YLW); LED_0603_1608Metric; LCSC C2290
FB1: 600R; L_0603_1608Metric; LCSC C1002
J5: USB_C_Female_USB2_Small; USB_C_DB-108PWB; LCSC C5178541
J6: SWD_B; SWD_PinHeader_1x04_P2.54mm_Horizontal_SMD; Digikey 952-3233-ND
R20, R21, R24: 100k; R_0603_1608Metric; LCSC C25803
R22, R23: 5.1k; R_0603_1608Metric; LCSC C23186
R25: 22k; R_0603_1608Metric; LCSC C31850
R26: 47k; R_0603_1608Metric; LCSC C25819
R27: 1k; R_0603_1608Metric; LCSC C21190
R28: 680R; R_0603_1608Metric; LCSC C23228
R29, R30: 10k; R_0603_1608Metric; LCSC C25804
SW1: SW_STM_RESET; SW_Push_1P1T_XKB_TS-1187A; LCSC C318884
SW2: SW_STM_BOOT_MODE; SW_Push_1P1T_XKB_TS-1187A; LCSC C318884
U13: CP2102N-A02-GQFN20R; QFN-20-1EP_3x3mm; LCSC C969913
U14: STM32F103CBT6; LQFP-48_7x7mm_P0.5mm; LCSC C8304
U15: TCAN1051HGVDR; SOIC_1044BDR_TEX; Digikey 296-44225-1-ND
U16: BY25Q128ES; SOIC-8_5.23x5.23mm_P1.27mm; Digikey 5369-BY25Q128ESSIG(R)CT-ND
Y1: X322516MMB4SI; Crystal_SMD_3225-4Pin_3.2x2.5mm; LCSC C13738

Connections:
3.3VA: C43.1, C44.1, FB1.1, U14.9 (VDDA)
3.3V_ACS_PWR: U14.14 (PA4); also elsewhere on the board
3.3V_CURR_SENSE: U14.12 (PA2); also elsewhere on the board
3.3V_MUX: C38.2, C39.2, C40.1, C41.2, C42.2, C45.1, C47.1, C48.1, FB1.2, R21.2, R27.2, R29.2, R30.2, SW2.2, U13.6 (VDD), U13.7 (VREGIN), U14.1 (VBAT), U14.24 (VDD), U14.36 (VDD), U14.48 (VDD), U15.5 (VIO), U16.8 (VCC); also elsewhere on the board
3.3V_SWD: J6.2 (3V3); also elsewhere on the board
5V_ACS_PWR: U14.16 (PA6); also elsewhere on the board
5V_CURR_SENSE: U14.15 (PA5); also elsewhere on the board
5V_PSU: C46.1, U15.3 (VCC); also elsewhere on the board
5V_SENSE: U14.11 (PA1); also elsewhere on the board
5V_USB: J5.A4 (VBUS), J5.A9 (VBUS), J5.B4 (VBUS), J5.B9 (VBUS), R25.2; also elsewhere on the board
24V_CURR_SENSE: U14.18 (PB0); also elsewhere on the board
BATT_SENSE: U14.10 (PA0); also elsewhere on the board
BOOT0: R20.2, SW2.1, U14.44 (BOOT0)
BOOT1: R24.2, U14.20 (PB2)
CAN_N: U15.6 (CANL); also elsewhere on the board
CAN_P: U15.7 (CANH); also elsewhere on the board
CAN_RX: U14.45 (PB8), U15.4 (RXD)
CAN_TX: U14.46 (PB9), U15.1 (TXD)
DB_LED: R28.2, U14.17 (PA7)
GND: C33.2, C34.2, C35.2, C36.1, C38.1, C39.1, C40.2, C41.1, C42.1, C43.2, C44.2, C45.2, C46.2, C47.2, C48.2, D8.1 (K), J5.A1 (GND), J5.A12 (GND), J5.B1 (GND), J5.B12 (GND), J6.1 (GND), R20.1, R22.2, R23.2, R24.1, R26.1, SW1.1, U13.3 (GND), U13.12 (GND), U13.21 (GND), U14.8 (VSSA), U14.23 (VSS), U14.35 (VSS), U14.47 (VSS), U15.2 (GND), U16.1 (~CS), U16.4 (GND), Y1.2, Y1.4; also elsewhere on the board
GSE_SENSE: U14.19 (PB1); also elsewhere on the board
MISO_FL: U14.27 (PB14), U16.2 (DO(IO1))
MOSI_FL: U14.28 (PB15), U16.5 (DI(IO0))
unnamed: D8.2 (A), R28.1
unnamed: J5.A5 (CC1), R22.1
unnamed: J5.B5 (CC2), R23.1
unnamed: C36.2, R25.1, R26.2, U13.8 (VBUS)
unnamed: R27.1, U13.9 (~RST)
unnamed: R30.1, U16.3 (IO2)
OSC_IN: C33.1, U14.5 (PD0), Y1.1
OSC_OUT: C35.1, U14.6 (PD1), Y1.3
RESET_FL: R29.1, U14.25 (PB12), U16.7 (IO3)
SCK_FL: U14.26 (PB13), U16.6 (CLK)
STM_RESET: C34.1, R21.1, SW1.2, U14.7 (NRST)
SWCLK: J6.4 (SWCLK), U14.37 (PA14)
SWDIO: J6.3 (SWDIO), U14.34 (PA13)
USART_RX: U13.17 (RXD), U14.22 (PB11)
USART_TX: U13.18 (TXD), U14.21 (PB10)
USB_N: J5.A7 (D-), J5.B7 (D-), U13.5 (D-)
USB_P: J5.A6 (D+), J5.B6 (D+), U13.4 (D+)

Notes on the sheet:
STM32 Reset
STM32 decoupling caps; place close to 3.3V pins
NOTE: Not typtical CANT used, ISO1044BDR was out of stock
Vf=2.1V, I=1.8mA, R=680
CANBUS Interface
for next revision Fixed UART TX/RX polarity
Flash Module (SPI)
NOTE: Not typtical flash used, pins are identical but lower write speeds
Serial Wire Debug
Debug LED
B0 HIGH = PROGRAMMING MODE B0 LOW = RUN MEMORY
USB-UART Bridge
CL = (CLcrystal - Cstray)* 2 YXC XL7EL89CKI-111YLC-16M Crystal
Mount connector at edge of board
Crystal Oscillator
for next revision Added 3.3V reference to VIO
moved 10uF cap next to ideal diodes
STM32 Boot Mode
USB Connection
Additional Filtering for Analogue VDD
